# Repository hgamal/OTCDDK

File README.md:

# OTCDDK
OTCDDK means "Other Tone Core DSP Development Kit". It was enginered in order to permit develop DSP algorithms in other platforms such linux or Windows.

# Install and run on Windows
1. install git
2. if you want to compile dsp codes:
   1. download "make" from "https://sourceforge.net/projects/ezwinports/files/"
   2. install "make"  - downloaded above - into git mingw directory (mine is under C:\Program Files\Git\mingw32)
3. clone https://github.com/hgamal/OTCDDK.git
4. start git bash session under cloned directory

# tasks
## help
```
$ ./bin/tcddk-ctl
usage: ./tcddk-ctl [list|monitor|set_debug|upload_dsp]
```
## compile example dsp code: cd dsp-code/
```
$ cd dsp-code/TwoBandStereoEQ
$ make
```
## upload code to DSP
```
$ ./bin/cld2hex cld-exemples/TwoBandStereoEQ.cld
$ ./bin/tcddk-ctl upload_dsp cld-exemples/TwoBandStereoEQ.hex
Upload size=1101 (367 words)
Upload Checksum=e557
Upload size=1107
Upload Checksum=cba14
1107 bytes transfered
```
## monitor DSP running (pots and switches)
```
$ ./bin/tcddk-ctl monitor
0024: p0=000, p1=000, p2=000, p3=000, p4=000, p5=000, s0=0, s1=0, tb=0, bb=0, gl=0, rl=0, dbg0=000000, dbg1=000000, dbg2=000000, dbg3=000000
```

- p0-p6: Potentiometer positions - values from 0 to 255

- s0-s1: Switches - values from 0, 1 and 2 (left, mid rigth)

- tb-bb: Top and Botton Switches - values 0 and 1

- gl-rl: Leds (green and red) - values 0 and 1

- dbg0 - dbg1: debug variables 24 bit resolution

## to upload code to mcu
not available yet

# udev configuration on linux
```
	# cat /etc/udev/rules.d/27-line6.rules
	#TCDDK
	SUBSYSTEM=="usb", ACTION=="add", ATTR{idVendor}=="0e41", ATTR{idProduct}=="4154", SYMLINK+="tcddk-%k", GROUP="line6"

	# udevadm control --reload-rules && udevadm trigger
```
# libusb windows
It is needed in order to compile tcddk-ctl.

Download libraries and sources from
	http://libusb.info/

## Installing WinUSB
In order to make tcddk-ctl work, the Tone COre Developer Line6 Interface must to be associated to Microsoft Winusb.sys. 
The follow these instructions to load the driver:

1. Plug in your device to the host system
2. Open Device Manager and locate the device
3. Right-click the device and select "Update driver software"
4. from the context menu. In the wizard, select "Browse my computer" for driver software
5. Select "Let me pick from a list of device drivers on my computer"
6. From the list of device classes, select "Universal Serial Bus devices"
7. The wizard displays WinUsb Device. Select it to load the driver.
	
# USB Vendor calls

## Get Version ?
	bmRequestType: 0xc0, bRequest: 67, wValue: 0x0000, wIndex: 0 (0x0000), wLength: 6
	return 6 bytes: c0:00:cf:ff:06:00

## Set debug variables to 800001800002800003800004
	bmRequestType: 0x40, bRequest: 65, wValue: 0x0000, wIndex: 0 (0x0000), wLength: 12, Data Fragment: 800001800002800003800004

## Erase Block
	bmRequestType: 0x40, bRequest: 99, wValue: 0xc000, wIndex: (c000, c200, c400, c600, c800, ca00, cc00, ce00) wLength: 1, Data Fragment: 00

## Get status
	bmRequestType: 0xc0, bRequest: 105, wValue: 0x0000, wIndex: 0 (0x0000), wLength: 1
	return 1 byte: 01 == success

## Program bytes
	bmRequestType: 0x40, bRequest: 97, wValue: start, wIndex: end, wLength: len, Data Fragment: bytes to program
	return 1 byte: 01 == success

## Send Checksum
	bmRequestType: 0xc0, bRequest: 66, wValue: {sum}, wIndex: 0 (0x0000), wLength: 1
	return 1 byte: 01 == success

## Read Status from DSP
	bmRequestType: 0xc0, bRequest: 64, wValue: 0x0000, wIndex: 0 (0x0000), wLength: 24
	return 64 bytes: pots, switches, buttons and debug variables

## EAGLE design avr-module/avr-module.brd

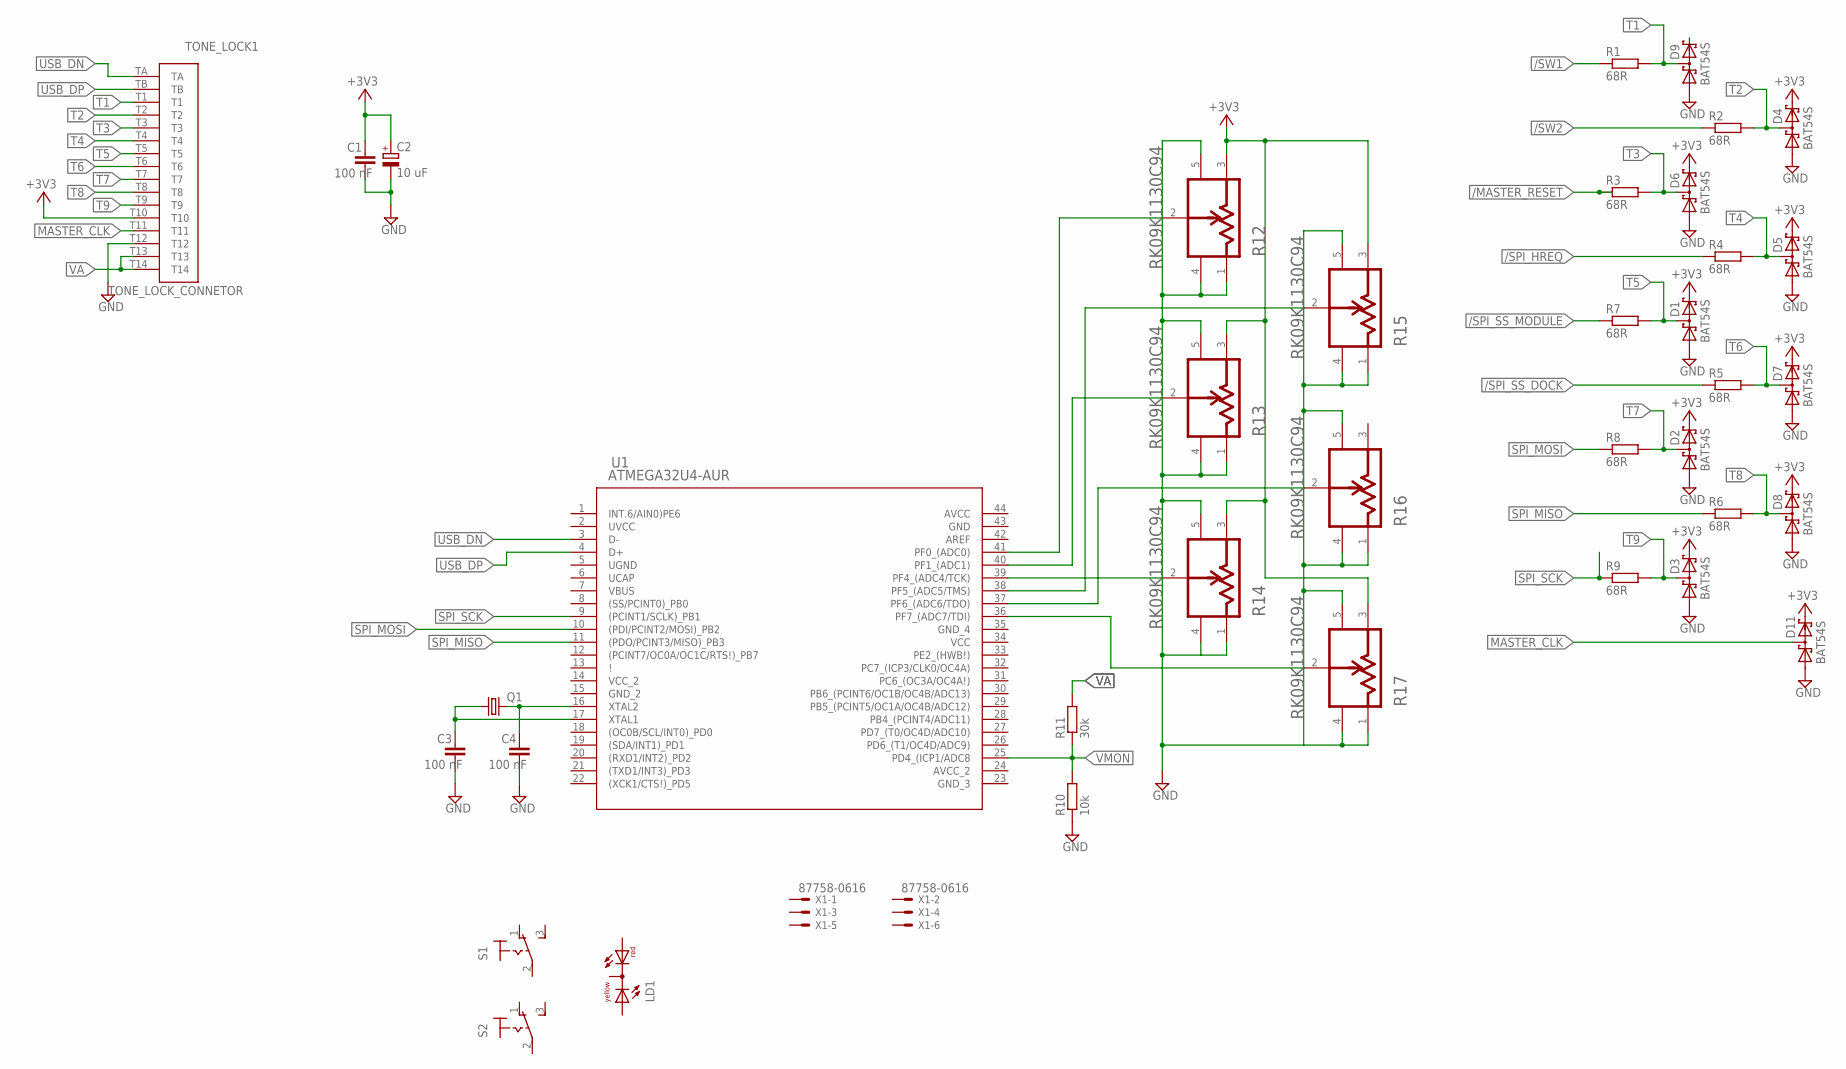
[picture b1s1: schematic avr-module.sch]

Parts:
C1, C3, C4: 100 nF; C0805
C2: 10 uF; UD-4X5,8_NICHICON
D1, D2, D3, D4, D5, D6, D7, D8, D9, D11: BAT54S; SOT23
LD1: DUOLED-RY-C; DUOLED-C-5MM
Q1: CRYSTALHC49S; HC49/S
R1, R2, R3, R4, R5, R6, R7, R8, R9: 68R; M1206
R10: 10k; M1206
R11: 30k; M1206
R12, R13, R14, R15, R16, R17: ALPS_ELECTRIC_CO.,_LTD._RK09K1130C94ALPS_ELECTRIC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; ALPS_ELECTRIC_CO.,_LTD._RK09K1130C94_0
S1, S2: 320-916
TONE_LOCK1: TONE_LOCK_CONNETOR; TONE_LOCK_CONNECTOR
U1: ATMEGA32U4-AUR; 44ML_ATM
X1: 87758-0616

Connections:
+3V3: C1.1, C2.+, D1.2 (C2), D2.2 (C2), D3.2 (C2), D4.2 (C2), D5.2 (C2), D6.2 (C2), D7.2 (C2), D8.2 (C2), D11.2 (C2), R12.3, R13.3, R14.3, R15.3, R17.3, TONE_LOCK1.T10
/MASTER_RESET: R3.1
/SPI_HREQ: R4.1
/SPI_SS_DOCK: R5.1
/SPI_SS_MODULE: R7.1
/SW1: R1.1
/SW2: R2.1
AVCC: U1.44 (AVCC)
AVCC_2: U1.24 (AVCC_2)
GND: C1.2, C2.-, C3.2, C4.2, D1.1 (A1), D2.1 (A1), D3.1 (A1), D4.1 (A1), D5.1 (A1), D6.1 (A1), D7.1 (A1), D8.1 (A1), D9.1 (A1), D11.1 (A1), R10.1, R12.1, R12.4 (MT1), R12.5 (MT2), R13.1, R13.4 (MT1), R13.5 (MT2), R14.1, R14.4 (MT1), R14.5 (MT2), R15.1, R15.4 (MT1), R15.5 (MT2), R16.1, R16.4 (MT1), R16.5 (MT2), R17.1, R17.4 (MT1), R17.5 (MT2), TONE_LOCK1.T12, U1.43 (GND)
GND_2: U1.15 (GND_2)
GND_3: U1.23 (GND_3)
GND_4: U1.35 (GND_4)
MASTER_CLK: D11.3 (C1A2), TONE_LOCK1.T11
unnamed: R12.2, U1.41 (PF0_(ADC0))
unnamed: R13.2, U1.40 (PF1_(ADC1))
unnamed: R14.2, U1.39 (PF4_(ADC4/TCK))
unnamed: R15.2, U1.38 (PF5_(ADC5/TMS))
unnamed: R16.2, U1.37 (PF6_(ADC6/TDO))
unnamed: R17.2, U1.36 (PF7_(ADC7/TDI))
unnamed: C4.1, Q1.2, U1.16 (XTAL2)
unnamed: C3.1, Q1.1, U1.17 (XTAL1)
SPI_MISO: R6.1, U1.11 ((PDO/PCINT3/MISO)_PB3)
SPI_MOSI: R8.1, U1.10 ((PDI/PCINT2/MOSI)_PB2)
SPI_SCK: R9.1, U1.9 ((PCINT1/SCLK)_PB1)
T1: D9.3 (C1A2), R1.2, TONE_LOCK1.T1
T2: D4.3 (C1A2), R2.2, TONE_LOCK1.T2
T3: D6.3 (C1A2), R3.2, TONE_LOCK1.T3
T4: D5.3 (C1A2), R4.2, TONE_LOCK1.T4
T5: D1.3 (C1A2), R7.2, TONE_LOCK1.T5
T6: D7.3 (C1A2), R5.2, TONE_LOCK1.T6
T7: D2.3 (C1A2), R8.2, TONE_LOCK1.T7
T8: D8.3 (C1A2), R6.2, TONE_LOCK1.T8
T9: D3.3 (C1A2), R9.2, TONE_LOCK1.T9
UCAP: U1.6 (UCAP)
UGND: U1.5 (UGND)
USB_DN: TONE_LOCK1.TA
USB_DP: TONE_LOCK1.TB
UVCC: U1.2 (UVCC)
VA: R11.2, TONE_LOCK1.T13, TONE_LOCK1.T14
VBUS: U1.7 (VBUS)
VCC: U1.34 (VCC)
VCC_2: U1.14 (VCC_2)
VMON: R10.2, R11.1, U1.25 (PD4_(ICP1/ADC8)

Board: 2 copper layers, 38 parts (3 on the bottom side), 25 nets, no tracks yet.

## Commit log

2018-03-10 project start
2018-03-10 more files
2018-03-10 tcddk control program first version
2018-03-10 binary files directory
2018-03-10 some comments
2018-03-10 comments
2018-03-11 License, Windows compilation and libusb
2018-03-11 CLD to HEX limited tool
2018-03-11 simple file conversion tools
2018-03-11 allow paths using spaces during DSP compile
2018-03-11 document better
2018-03-11 renaming example names
2018-03-12 latest binaries
2018-03-12 update documentation
2018-03-12 fixing upload and vanish debug messages on production environment
2018-03-19 install winusb driver instructions
2018-03-25 Fix some binary path issues
2018-03-25 make wine warning messages off
2018-03-25 new Delay example
2018-03-25 fixing execution attribute
2018-12-23 increasing delay implementation
2018-12-23 fix usage
2019-02-07 MOD: Some code beautify BUG: Do not open device, if it will not use it
2021-02-09 Fix device monitoring
2021-02-26 Creating a programming module with AVR
2021-02-26 Implementing "make test" for DSP CODE debugging
2021-02-26 Implementing "make install" for tcddk-ctl
2021-02-26 Reverting changes tha would conflict with standard MCU (hc08) code
2021-02-26 Add .gitignore
2021-03-06 more circuit changes
2021-03-08 More development
2021-03-10 work
2021-03-11 Clock correction
2021-03-13 Output 3 MHz
2021-03-18 Including LUFA project
2021-03-18 USB device created
2021-03-18 Fixing compilation warnings Fixing filenames with unnecessary capital letters
